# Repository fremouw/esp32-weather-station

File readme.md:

# ESP32 Weather Station

[ESP32](https://www.espressif.com/en/products/hardware/esp32/overview) based weather station. It shows four screens. 1) Current time and date (synced over NTP) 2) The current (local) weather conditions (data from the Weather underground) 3) 3-day forecast (also with data from the weather underground) 4) Current temperature, humidity, air pressure and, air quality (eCO2 and TVOC). This project was once based on https://github.com/squix78/esp8266-weather-station-platformio-demo, but most of it probably 90% is rewritten and targeted for the ESP32.

## Demo

## Software

Please see the config.example.h to configure your board.

## Hardware

My version uses a [2.42" OLED display](https://www.ebay.com/itm/SPI-2-42-OLED-128x64-Graphic-OLED-Module-Display-Arduino-PIC-AVR-Multi-wii/162156495387?ssPageName=STRK%3AMEBIDX%3AIT&_trksid=p2060353.m2749.l2649) over SPI. A Bosch BME280 chip for measuring the temperature, humidity and air pressure. The SGP30 is used to measure the air quality, eCO2 (equivalent calculated carbon-dioxide) and TVOC (Total Volatile Organic Compound) concentration. Both these sensors are attached using a 4-wire molex connector, to keep some distance from the board and display; as these generate some heat which influences the sensors.

The ESP32 board used is a DOIT ESP32 Devkit v1, you can find these on ebay.

### Schematic and board

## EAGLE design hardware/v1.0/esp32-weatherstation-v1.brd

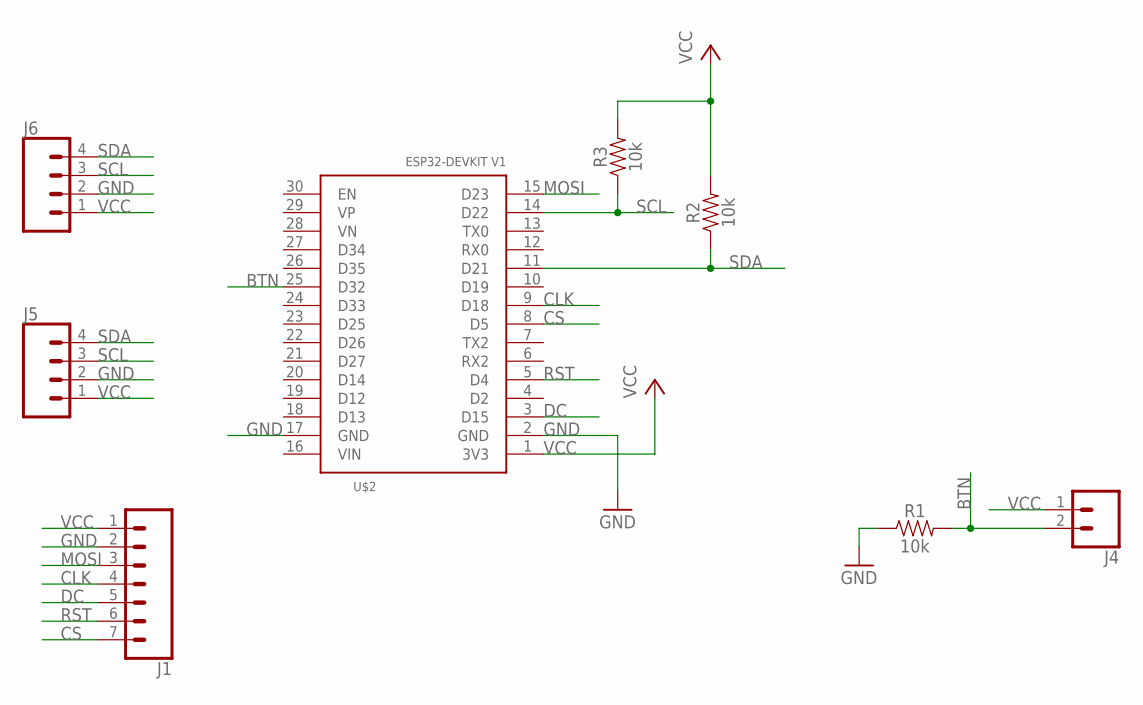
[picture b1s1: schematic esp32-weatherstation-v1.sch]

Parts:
J1: CONN_07; 1X07
J4: CONN_02; 1X02
J5, J6: CONN_04POLAR; MOLEX-1X4
R1, R2, R3: 10k; AXIAL-0.3
U$2: DOIT-ESP32DEVKIT1; ESP32-DEVKITV1

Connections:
BTN: J4.2, R1.P$2 (2), U$2.25 (D32)
CLK: J1.4, U$2.9 (D18)
CS: J1.7, U$2.8 (D5)
DC: J1.5, U$2.3 (D15)
GND: J1.2, J5.2, J6.2, R1.P$1 (1), U$2.2 (GND), U$2.17 (GND)
MOSI: J1.3, U$2.15 (D23)
RST: J1.6, U$2.5 (D4)
SCL: J5.3, J6.3, R3.P$1 (1), U$2.14 (D22)
SDA: J5.4, J6.4, R2.P$1 (1), U$2.11 (D21)
VCC: J1.1, J4.1, J5.1, J6.1, R2.P$2 (2), R3.P$2 (2), U$2.1 (3V3)

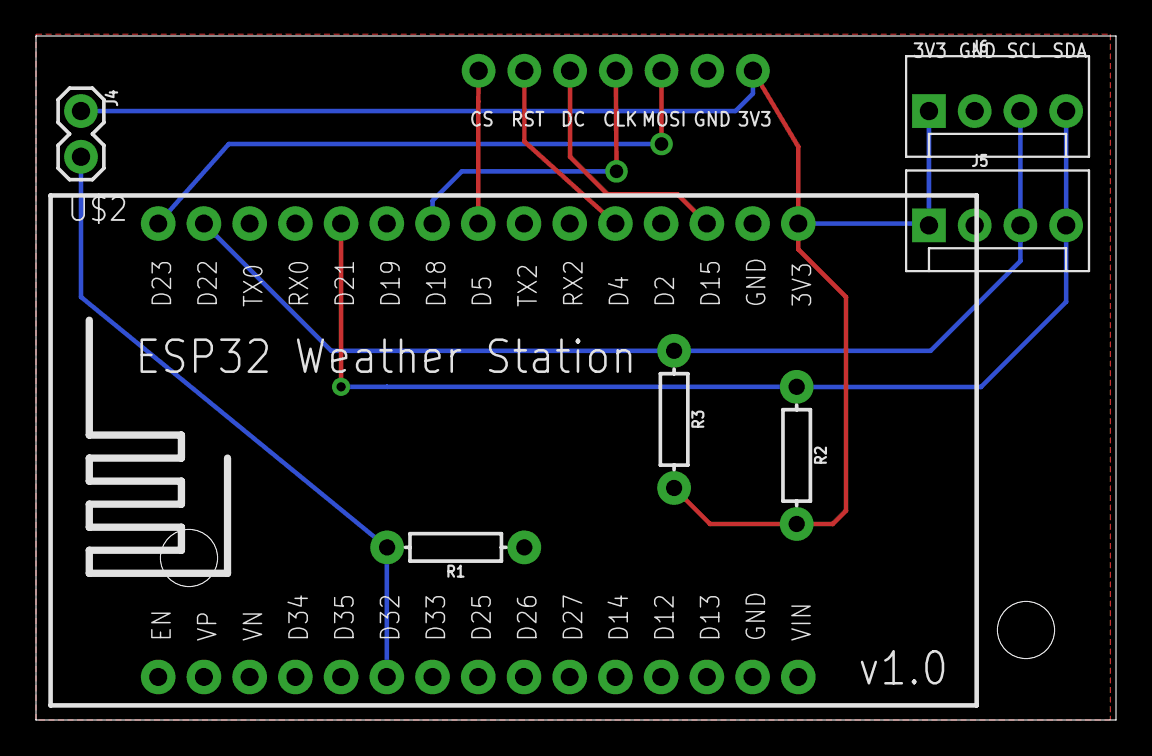
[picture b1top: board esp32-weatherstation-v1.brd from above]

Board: 2 copper layers, 60.0 x 38.0 mm, 8 parts (1 on the bottom side), 10 nets.

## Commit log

2018-02-17 first version.
2018-02-18 do not crash when unable to connect to NTP server.
2018-02-20 use multiple i2c busses, until timeouts are resolved with two devices on one bus.
2018-02-21 fix: return current unixtime.
2018-02-21 moved all config to config.h.
2018-02-21 cleanup
2018-02-21 set submodule to correct url.
2018-02-21 cleanup.
2018-02-21 pushing temperature/humidity/pressure to mqtt broker is optional.
2018-02-21 more cleanup.
2018-02-21 check if temperature was actually read.
2018-02-21 add timeout to temperature measurement.
2018-02-22 set i2c bus for bme280 to 100kHz
2018-02-22 get more accurate readings.
2018-02-23 use delta of last and current temperature measurement to check if the reading makes sense.
2018-04-05 SPI + SGP30 test.
2018-04-05 fixed SGP30 readings.
2018-08-18 working with spi.
2018-08-18 disable ssl
2018-08-19 add air quality sensor
2018-08-19 show air quality readings on display
2018-08-19 updated example config
2018-08-19 minor fix in displaying air quality
2018-08-19 clean up
2018-08-19 since we run the display now over SPI, we can move the sensor reading to the background task.
2018-08-19 small memory usage improvements.
2018-08-19 wip: ota updates.
2018-08-19 read air quality baseline every 5 minutes.
2018-08-19 add SGP lib as submodule
2018-08-19 switch to new commit of SGP lib.
2018-08-19 move sensor readings to main loop, seems to generate errors when running on 2nd cpu.
2018-08-20 Set time from NTP server async.
2018-08-21 Store the baseline of the air quality sensor in the EEPROM after pressing a button.
2018-08-21 move this to the config file.
2018-08-23 Increased MQTT packet size to 256bytes. With the eCO2 and TVOC added to the JSON packets became >128bytes which is more then the default packet size of the PubSub client.
2018-08-23 small code cleanup.
2018-09-13 Looks like compensation parameters are 28 bytes.
2018-09-13 disable SSL for wunderground API calls.
2018-09-13 add SSD1306 lib as submodule.
2018-09-13 no message
2018-09-13 add some debug logging
2018-09-13 rewrite of most of the code, most if it now is async.
2018-09-13 added schematics and board.
2018-09-13 added a readme.
2018-09-13 added missing config option.
2018-09-13 added screens of schematic and board.
2018-09-14 only show time and weather report when there's data.
2018-09-14 Only show log line when there's data to push to the broker.
2018-09-14 add AsyncTCP as submodule
2018-09-25 add rx timeout.
2018-09-25 update to new asynctcp branch for esp-idf update
2018-09-25 changed priority and decreased stack size.
2018-09-25 round temperatures in 3 day forecast to integers.
2018-09-25 add comment and some extra logging
2019-01-07 switch to stable espressif32 platform.
2019-01-07 not avail in stable.

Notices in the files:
parts and their libraries:
SparkFun-Connectors: Licensing: Creative Commons ShareAlike 4.0 International - https://creativecommons.org/licenses/by-sa/4.0
